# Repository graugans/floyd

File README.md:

# Project Floyd

This is a STM32F042 breakout board. The main feature of this board is the TSSOP 20 version of the CPU and the USB interface

# License (MIT)

Copyright (c) 2016 Christian Ege

Permission is hereby granted, free of charge, to any person obtaining a copy of this software and associated documentation files (the "Software"), to deal in the Software without restriction, including without limitation the rights to use, copy, modify, merge, publish, distribute, sublicense, and/or sell copies of the Software, and to permit persons to whom the Software is furnished to do so, subject to the following conditions:

The above copyright notice and this permission notice shall be included in all copies or substantial portions of the Software.

THE SOFTWARE IS PROVIDED "AS IS", WITHOUT WARRANTY OF ANY KIND, EXPRESS OR IMPLIED, INCLUDING BUT NOT LIMITED TO THE WARRANTIES OF MERCHANTABILITY, FITNESS FOR A PARTICULAR PURPOSE AND NONINFRINGEMENT. IN NO EVENT SHALL THE AUTHORS OR COPYRIGHT HOLDERS BE LIABLE FOR ANY CLAIM, DAMAGES OR OTHER LIABILITY, WHETHER IN AN ACTION OF CONTRACT, TORT OR OTHERWISE, ARISING FROM, OUT OF OR IN CONNECTION WITH THE SOFTWARE OR THE USE OR OTHER DEALINGS IN THE SOFTWARE.

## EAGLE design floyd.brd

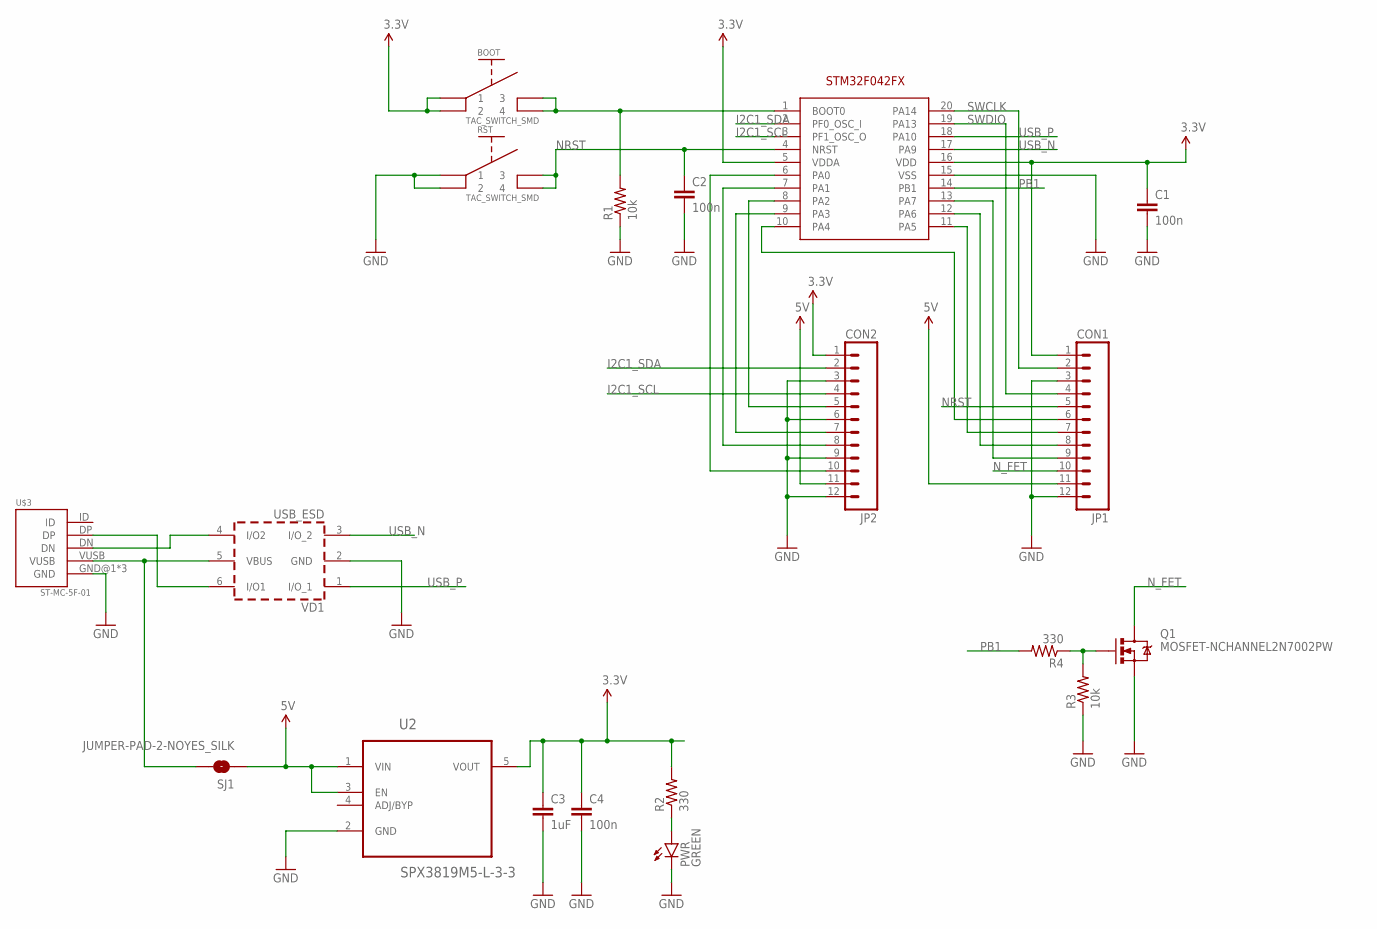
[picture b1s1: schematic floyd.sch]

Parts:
BOOT: TS-017A; TS-017ASMD
C1, C2, C4: 100n; 0603-CAP
C3: 1uF; 0603-CAP
JP1: CON1; 1X12_LOCK_LONGPADS
JP2: CON2; 1X12_LOCK_LONGPADS
PWR: GREEN; LED-0603
Q1: MOSFET-NCHANNEL2N7002PW; SOT323
R1, R3: 10k; 0603-RES
R2, R4: 330; 0603-RES
RST: TS-017A; TS-017ASMD
SJ1: JUMPER-PAD-2-NOYES_SILK; PAD-JUMPER-2-NO_YES_SILK
U1: STM32F042FX; TSSOP20
U2: SPX3819M5-L-3-3; SOT95P280X145-5N
U$3: ST-MC-5F-01
VD1: USB_ESD; SOT-23-6L

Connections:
3.3V: BOOT.P$1 (1), BOOT.P$2 (2), C1.1, C3.1, C4.1, JP1.1, JP2.1, R2.2, U1.5 (VDDA), U1.16 (VDD), U2.5 (VOUT)
5V: JP1.11, JP2.11, SJ1.1, U2.1 (VIN), U2.3 (EN)
GND: C1.2, C2.2, C3.2, C4.2, JP1.3, JP1.12, JP2.3, JP2.6, JP2.9, JP2.12, PWR.C, Q1.2 (S), R1.1, R3.1, RST.P$1 (1), RST.P$2 (2), U1.15 (VSS), U2.2 (GND), U$3.GND@1 (GND), U$3.GND@2 (GND), U$3.GND@3 (GND), VD1.2 (GND)
I2C1_SCL: JP2.4, U1.3 (PF1_OSC_O)
I2C1_SDA: JP2.2, U1.2 (PF0_OSC_I)
unnamed: BOOT.P$3 (3), BOOT.P$4 (4), R1.2, U1.1 (BOOT0)
unnamed: SJ1.2, U$3.VUSB, VD1.5 (VBUS)
unnamed: U$3.DN, VD1.4 (I/O2)
unnamed: U$3.DP, VD1.6 (I/O1)
unnamed: JP1.6, U1.10 (PA4)
unnamed: JP1.7, U1.11 (PA5)
unnamed: PWR.A, R2.1
unnamed: JP1.8, U1.12 (PA6)
unnamed: JP1.9, U1.13 (PA7)
unnamed: Q1.1 (G), R3.2, R4.1
unnamed: JP2.5, U1.8 (PA2)
unnamed: JP2.7, U1.9 (PA3)
unnamed: JP2.8, U1.7 (PA1)
unnamed: JP2.10, U1.6 (PA0)
NRST: C2.1, JP1.5, RST.P$3 (3), RST.P$4 (4), U1.4 (NRST)
N_FET: JP1.10, Q1.3 (D)
PB1: R4.2, U1.14 (PB1)
SWCLK: JP1.2, U1.20 (PA14)
SWDIO: JP1.4, U1.19 (PA13)
USB_N: U1.17 (PA9), VD1.3 (I/O_2)
USB_P: U1.18 (PA10), VD1.1 (I/O_1)

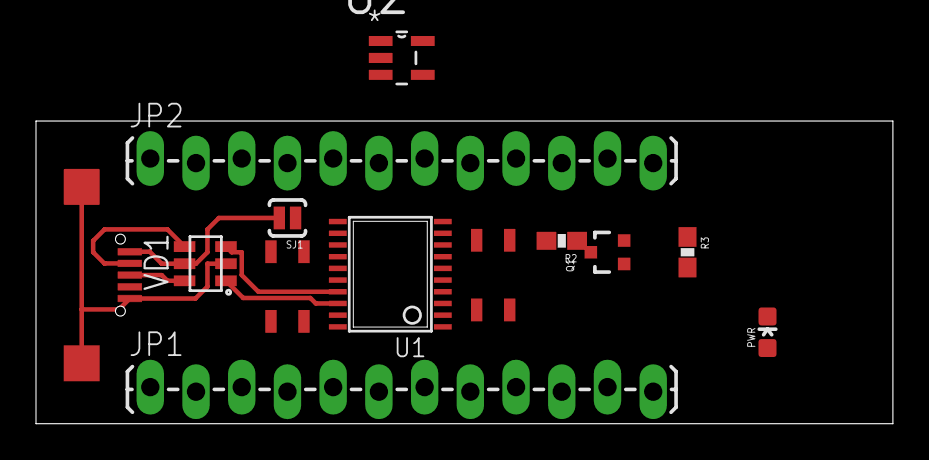
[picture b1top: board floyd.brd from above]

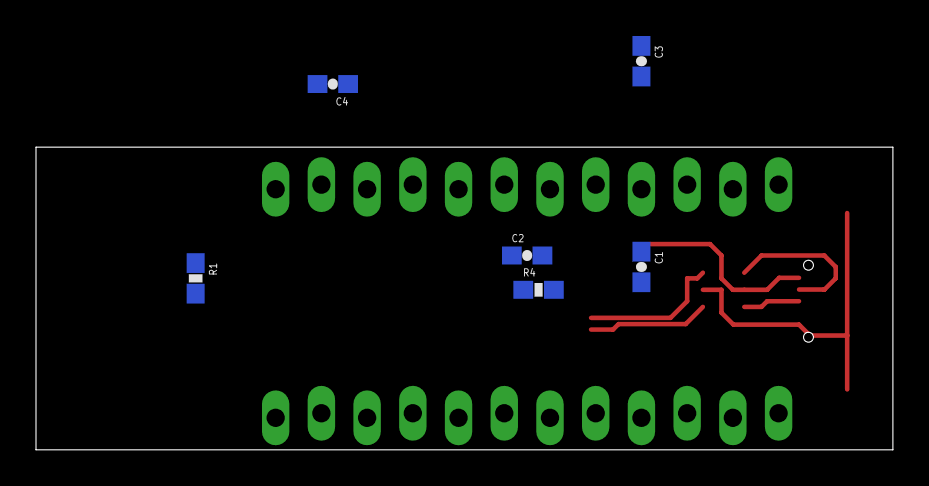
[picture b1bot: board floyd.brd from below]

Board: 2 copper layers, 47.6 x 16.8 mm, 19 parts (6 on the bottom side), 26 nets.

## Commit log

2016-03-25 Initial Version of Project Floyd
2016-03-25 Moved libraries to lib folder

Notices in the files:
parts and their libraries:
SparkFun-Passives: Licensing: Creative Commons ShareAlike 4.0 International - https://creativecommons.org/licenses/by-sa/4.0
